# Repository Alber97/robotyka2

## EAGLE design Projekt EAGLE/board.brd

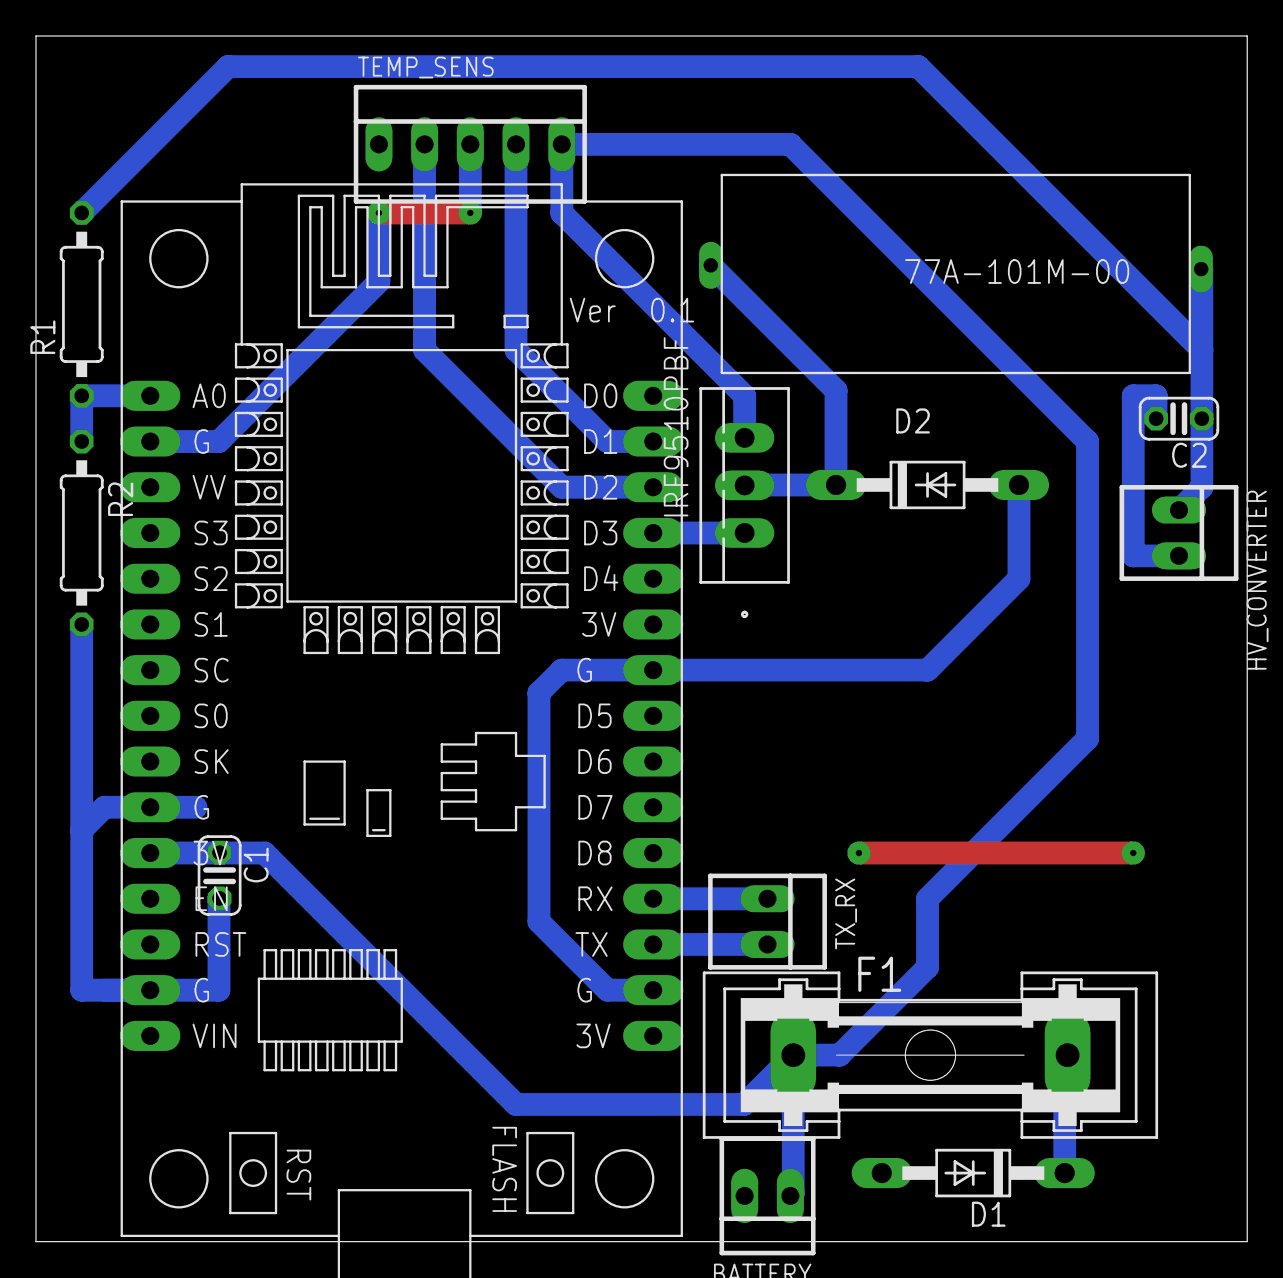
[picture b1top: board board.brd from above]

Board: 2 copper layers, 67.3 x 67.0 mm, 14 parts (0 on the bottom side), 12 nets.

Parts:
BATTERY: 22-23-2021
C1, C2: C025-024X044
D1, D2: 1N4004LONGFOOTPRINT; LONGFOOTPRINT
F1: GSH15
HV_CONVERTER: 22-23-2021
R1, R2: 0207/10
TEMP_SENS: 22-23-2051
TX_RX: 22-23-2021
U1: IRF9510PBFIRF95110PBF; IRF9510PBF
U$1: NODEMCU
U$2: 77A-101M-00

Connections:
3V: U$1.16, U$1.25
GND: BATTERY.2, C1.2, C2.2, D1.A, D2.A, HV_CONVERTER.2, R2.2, TEMP_SENS.3, U$1.2, U$1.10, U$1.14, U$1.17, U$1.24
unnamed: D1.C, F1.2
unnamed: D2.C, U1.2, U$2.1
unnamed: TX_RX.1, U$1.19
unnamed: TX_RX.2, U$1.18
unnamed: R1.1, R2.1, U$1.1
PWM: U1.1, U$1.27
REG_OUT: C2.1, HV_CONVERTER.1, R1.2, U$2.2
SCLK: TEMP_SENS.4, U$1.29
SDA: TEMP_SENS.2, U$1.28
V_BATT: BATTERY.1, C1.1, F1.1, TEMP_SENS.5, U1.3, U$1.11

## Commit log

2021-02-22 Inital commit
2021-02-22 Dodanie danych pomiarowych
2021-02-22 Dodanie projektu EAGLE
